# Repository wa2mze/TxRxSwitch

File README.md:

# TxRxSwitch
Mosfet power transmit/receive power switch for ham qrp rig

This little goodie will be used in a ubitx clone I'm designing. It was my first attempt at creating a pcb with Kicad.
Project uses some kicad libraries from Digikey.

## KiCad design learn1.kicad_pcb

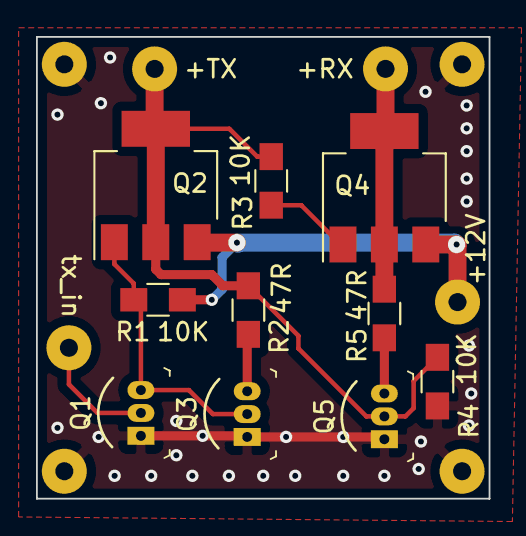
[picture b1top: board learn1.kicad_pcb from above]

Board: 2 copper layers, 25.1 x 25.7 mm, 18 parts (0 on the bottom side), 9 nets.

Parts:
J1: 12VoltIn; SolderWirePad_single_1mmDrill
J2: +RXout; SolderWirePad_single_1mmDrill
J3: +TXout; SolderWirePad_single_1mmDrill
J4: tx_in; SolderWirePad_single_1mmDrill
J5, J6, J7, J8: GND; SolderWirePad_single_1mmDrill
Q1, Q3, Q5: 2N7000; TO-92-3
Q2, Q4: NDT2955; SOT-223-3_TabPin2
R1, R3: 10K; R_0805_HandSoldering
R2, R5: 47; R_0805_HandSoldering
R4: 100K; R_0805_HandSoldering

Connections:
+12V: J1.1, Q2.3, Q4.3, R1.1
+RX: J2.1, Q4.2, R5.1
+TX: J3.1, Q2.2, Q5.2, R2.1, R3.2, R4.2
GND: J5.1, J6.1, J7.1, J8.1, Q1.1, Q3.1, Q5.1, R4.1
unnamed: Q1.3, Q2.1, Q3.2, R1.2
unnamed: Q3.3, R2.2
unnamed: Q4.1, R3.1
unnamed: Q5.3, R5.2
tx: J4.1, Q1.2

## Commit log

2020-05-20 Add files via upload
    My first Kicad project, so it was named "learn1".
2020-05-21 Add files via upload
    schematic in pdf

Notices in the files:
learn1.kicad_pcb:
Copyright (c)
